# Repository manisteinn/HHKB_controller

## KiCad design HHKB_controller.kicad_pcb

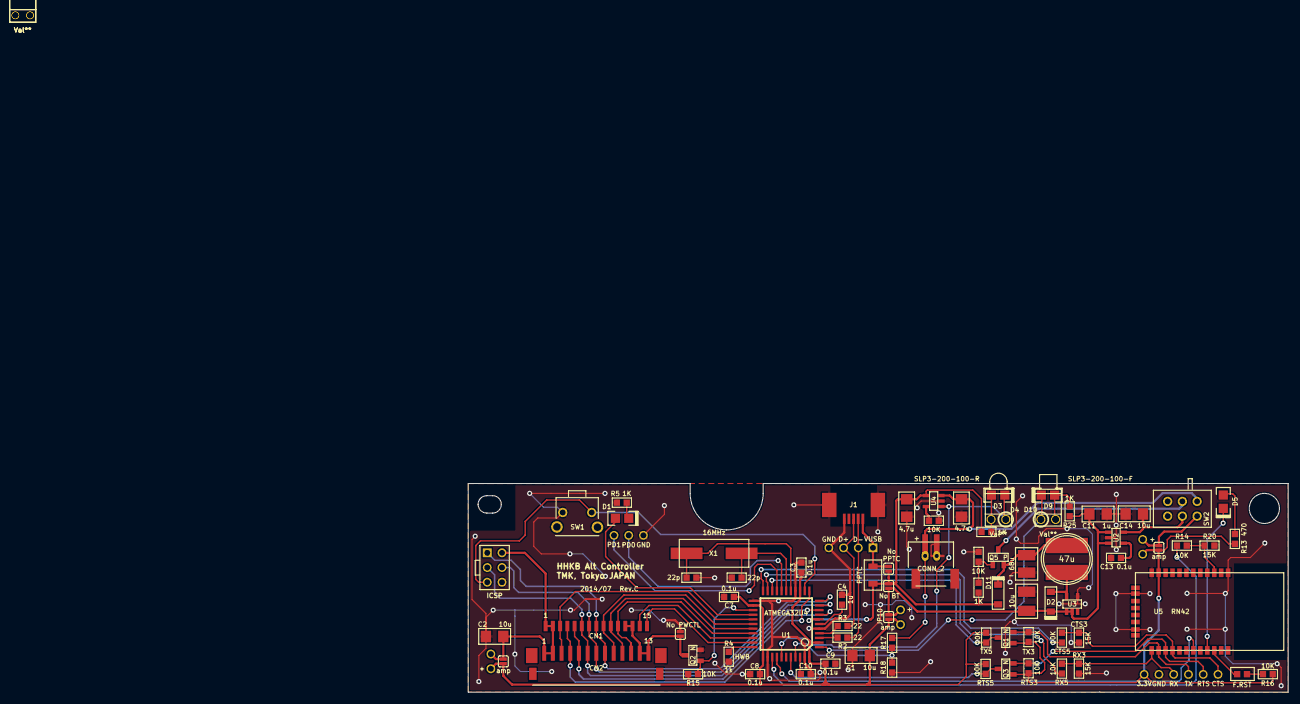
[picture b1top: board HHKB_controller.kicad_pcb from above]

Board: 2 copper layers, 141.5 x 36.0 mm, 98 parts (0 on the bottom side), 60 nets.

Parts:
C1, C2, C14: 10u; C_3216
C3, C7, C8, C9, C10, C13: 0.1u; C_1608
C4: 1u; C_1608
C5, C6: 22p; C_1608
C11: 1u; C_3216
C12: 10u; C_3228
C15: 68u; C_3225
C16, C18: 4.7u; C_3216
CN1: CONN_15; HHKB_JP_HRS_DF14_15P
CN2: CONN_13; HHKB_PRO2_ZH13
D1, D3, D5, D9: LED; LED_2012_HSOL
D2, D11: Schottky diode; D_SOD123
D4, D10: LED; LED_TH
J1: USB_mini_micro_B; USB_miniB_hirose_new
JP1, JP2, JP3, JP10, JP11, JP12: JUMPER; SOLDER_JUMPER_2
L1: 47u; L_7x7MM
P1, P7: GND; PIN_1
P2: D+; PIN_1
P3: D-; PIN_1
P4: VUSB; PIN_1_SQUARE
P5: PD1; PIN_1
P6: PD0; PIN_1
P8: CONN_3X2; AVR_ICSP_3x2
P9, P10, P11, P12, P110, P111, P112, P113, P114, P115, P130, P131: CONN_1; PIN_1
P100: CONN_2; JST_PH2_SMT_TH
PPTC1: PPTC; PPTC_nano
Q1, Q2, Q3: N; MOS_FET_SOT23-3_HSOL
Q5: P; MOS_FET_SOT23-3_HSOL
R1, R6, R7, R8, R11, R12, R14, R15, R16, R22, R23: 10K; R_1608
R2, R3: 22; R_1608
R4: 1k; R_1608
R5, R10, R21, R25: 1K; R_1608
R9, R20, R24: 15K; R_1608
R13: 470; R_1608
R17, R18: R; R_1608
R19: F.RST; R_1608_NOGUIDE
SLP3-200-100-F, SLP3-200-100-R, SLP3-200-100-R#2: Val**; SLP3-200-100-F
SLP3-200-100-R#3: Val**; SLP3-200-100-R
SW1: SW_PUSH; SW_TACT_TH_HORIZ_LOW
SW2: SW_DPDT; SW_MINI_SLIDE
U1: ATMEGA32U4; QFP44
U2: TAR5SB33; SOT23-5_HSOL
U3: NCP1402; SOT23-5_HSOL
U4: MCP73831; SOT23-5_HSOL
U5: RN42
X1: 16MHz; HC-49_SMT

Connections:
5V_BOOST: C1.1, C2.1, C3.1, C7.1, C8.1, C9.1, C11.1, C12.1, CN1.1, CN1.2, CN2.1, CN2.2, D2.2, JP2.2, JP10.1, JP10.2, JP11.1, JP11.2, P8.2, P9.1, P10.1, P11.1, P12.1, R7.1, R12.1, R15.1, R25.1, U1.2, U1.14, U1.24, U1.34, U1.44, U2.1, U2.3, U3.1, U3.2
+3.3V: JP12.1, JP12.2, P110.1, P130.1, P131.1, Q1.G, Q3.G, R1.1, R6.1, R13.1, R16.1, SW2.5, U5.11
/AREF: C10.1, U1.42
/D+: J1.3, P2.1, R3.2
/D-: J1.2, P3.1, R2.2
/HHKB_GND: CN1.12, CN1.13, CN2.12, CN2.13, JP3.2, Q2.D
/PB0: CN1.5, CN2.5, U1.8
/PB1: CN1.6, CN2.6, P8.3, U1.9
/PB2: CN1.7, CN2.7, P8.4, U1.10
/PB3: CN1.8, CN2.8, P8.1, U1.11
/PB4: CN1.9, CN2.9, U1.28
/PB5: CN1.10, CN2.10, U1.29
/PB6: CN1.11, CN2.11, U1.30
/PB7: CN1.4, CN2.4, U1.12
/PC6: CN1.14, U1.31
/PC7: CN1.15, U1.32
/PD0: P6.1, U1.18
/PD1: P5.1, U1.19
/PD4: Q2.G, R15.2, U1.25
/PD6: D1.1, U1.26
/PD7: CN1.3, CN2.3, U1.27
/VUSB_RAW: J1.1, JP1.1, P4.1, PPTC1.1
/bluetooth/3.3V_OUT: C14.1, SW2.4, U2.5
/bluetooth/CONN: R14.2, R20.1, U5.3
/bluetooth/CTS_33: P114.1, R23.2, R24.1, U5.16
/bluetooth/FACTORY_RESET: R19.2, U5.22
/bluetooth/LED_STS: D5.2, U5.21
/bluetooth/LIPO_RAW: C16.1, P100.1, R17.1, SW2.2, U4.3
/bluetooth/LIPO_SW: Q5.D, SW2.1
/bluetooth/PSEL: C15.1, D11.2, L1.2, Q5.S
/bluetooth/RTS_33: P115.1, Q3.S, R1.2, U5.15
/bluetooth/RX_33: P111.1, R8.2, R9.1, U5.13
/bluetooth/TX_33: P112.1, Q1.S, R6.2, U5.14
/~RESET: P8.5, SW1.2, U1.13
BT_CONN: R14.1, U1.36
BT_CTS: R23.1, U1.22
BT_INDICATOR: D9.2, D10.2, U1.1
BT_RTS: Q3.D, R12.2, U1.40
BT_RX: R8.1, U1.21
BT_TX: Q1.D, R7.2, U1.20
GND: C1.2, C2.2, C3.2, C4.2, C5.2, C6.2, C7.2, C8.2, C9.2, C10.2, C11.2, C12.2, C13.2, C14.2, C15.2, C16.2, C18.2, J1.5, J1.6, JP3.1, P1.1, P7.1, P8.6, P100.2, P113.1, Q2.S, R4.1, R5.2, R9.2, R11.2, R18.2, R20.2, R22.2, R24.2, SW1.1, U1.5, U1.15, U1.23, U1.35, U1.43, U2.2, U3.4, U4.2, U5.1, U5.12, U5.28, U5.29
LINKED: U1.37, U5.19
LIPO_SENSE: R17.2, R18.1, U1.41
unnamed: C4.1, U1.6
unnamed: C5.1, U1.16, X1.1
unnamed: C6.1, U1.17, X1.2
unnamed: C13.1, U2.4
unnamed: D1.2, R5.1
unnamed: D2.1, L1.1, U3.5
unnamed: D3.1, D4.1, R10.1
unnamed: D5.1, R13.2
unnamed: D9.1, D10.1, R25.2
unnamed: Q5.G, R21.2, R22.1
unnamed: R2.1, U1.3
unnamed: R3.1, U1.4
unnamed: R4.2, U1.33
unnamed: R11.1, U4.5
unnamed: R16.2, R19.1
VUSB: C18.1, D11.1, JP1.2, JP2.1, PPTC1.2, R10.2, R21.1, U1.7, U4.4
~CHRG: D3.2, D4.2, U1.38, U4.1

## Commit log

2014-08-03 SLP3.mod added, components added to board
